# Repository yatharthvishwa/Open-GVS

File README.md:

# Open-GVS
control a person with gvs!!
this can control your balance by applying a controlled current to your mastoids, this project uses diy 3d printed electrodes which you can apply to your mastoids which are connected to the pcb
I was inspired to make this project because of a open sauce video https://www.youtube.com/watch?v=9Om2X6QcTgw

how to use?

📄 [View BOM](./GVS.csv)

electrode stl

PCB

Simulation

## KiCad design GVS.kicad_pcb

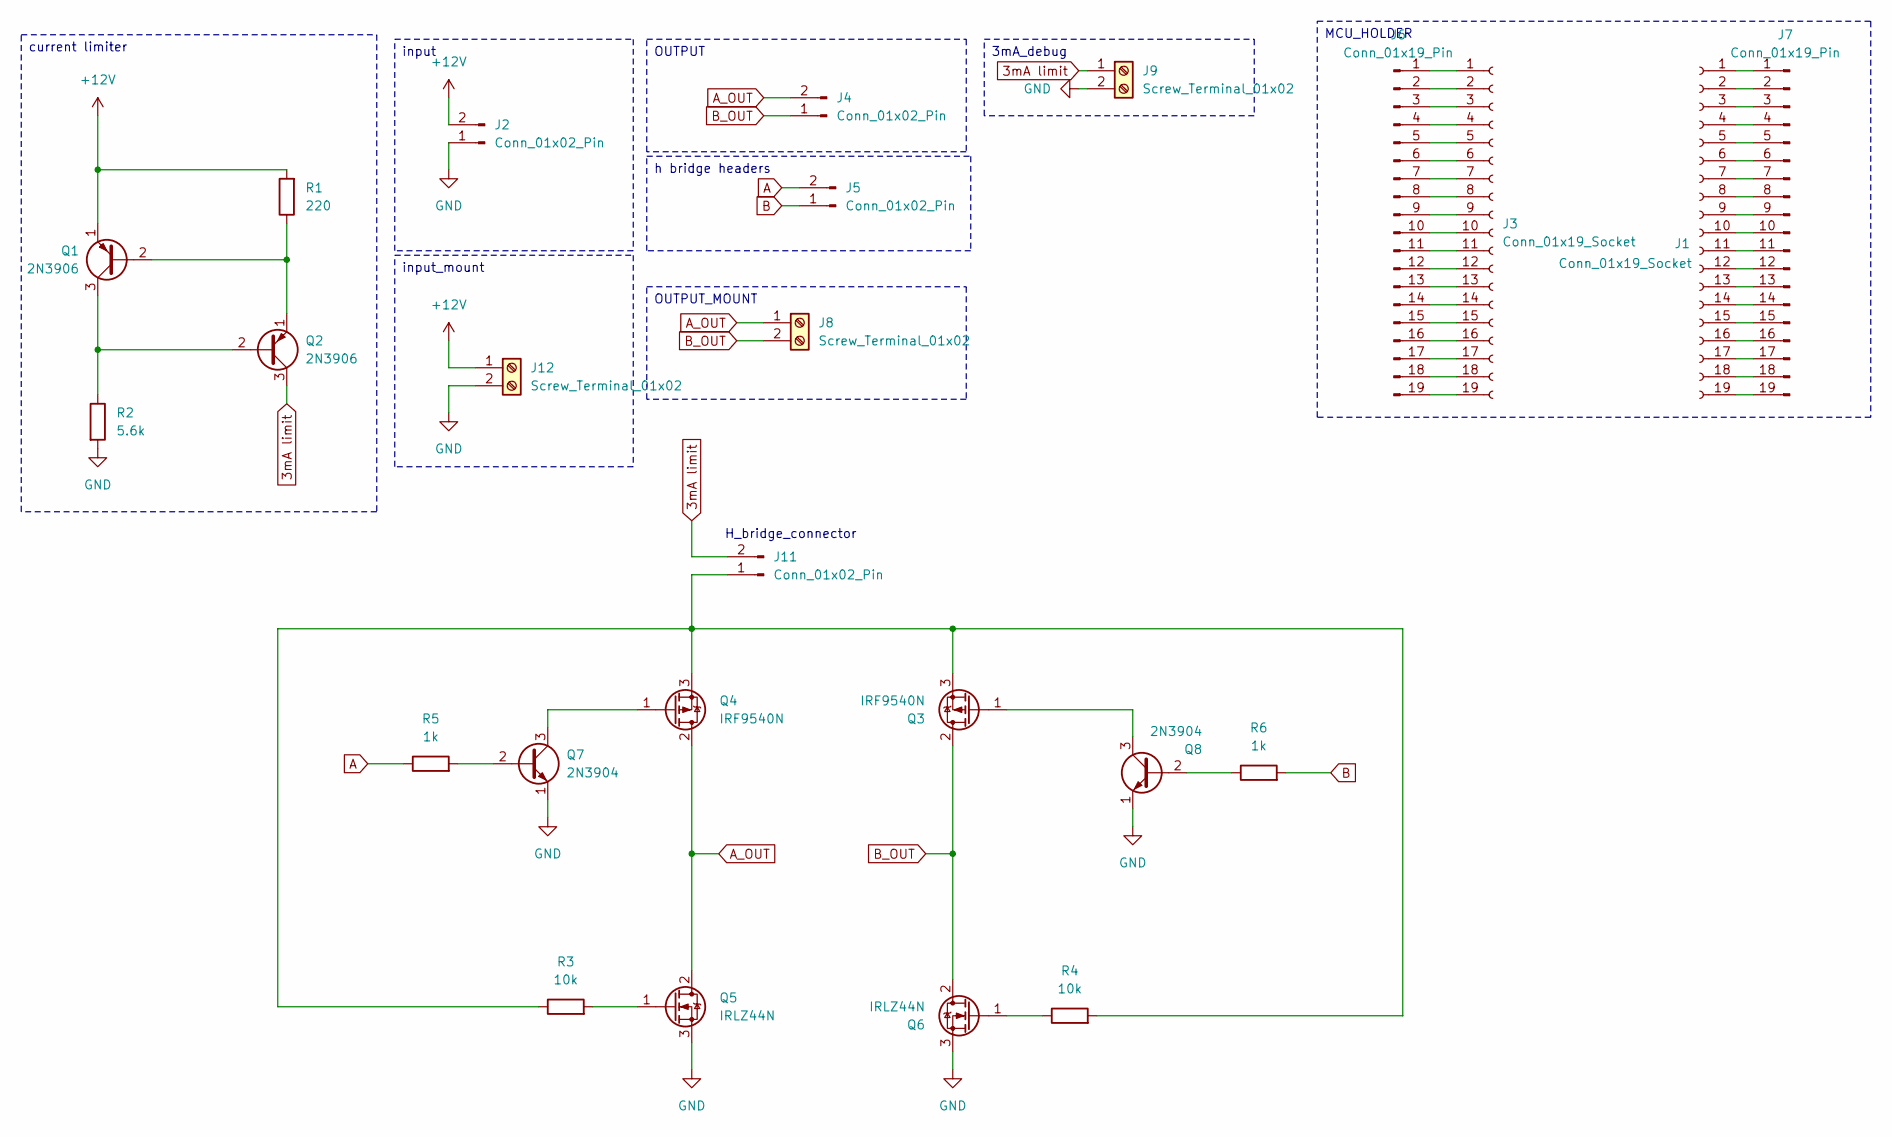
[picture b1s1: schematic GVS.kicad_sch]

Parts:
J1, J3: Conn_01x19_Socket; PinSocket_1x19_P2.54mm_Vertical
J2, J4, J5, J11: Conn_01x02_Pin; PinHeader_1x02_P2.54mm_Vertical
J6, J7: Conn_01x19_Pin; PinHeader_1x19_P2.54mm_Vertical
J8, J9, J12: Screw_Terminal_01x02; TerminalBlock_Xinya_XY308-2.54-2P_1x02_P2.54mm_Horizontal
Q1, Q2: 2N3906; TO-92_Inline
Q3, Q4: IRF9540N; TO-220-3_Vertical
Q5, Q6: IRLZ44N; TO-220-3_Vertical
Q7, Q8: 2N3904; TO-92_Inline
R1: 220; R_Axial_DIN0204_L3.6mm_D1.6mm_P2.54mm_Vertical
R2: 5.6k; R_Axial_DIN0204_L3.6mm_D1.6mm_P2.54mm_Vertical
R3, R4: 10k; R_Axial_DIN0204_L3.6mm_D1.6mm_P2.54mm_Vertical
R5, R6: 1k; R_Axial_DIN0204_L3.6mm_D1.6mm_P2.54mm_Vertical

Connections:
3mA limit: J9.1, J11.2, Q2.3 (C)
+12V: J2.2, J12.1, Q1.1 (E), R1.2
A: J5.2, R5.1
A_OUT: J4.2, J8.1, Q4.2 (D), Q5.2 (D)
B: J5.1, R6.2
B_OUT: J4.1, J8.2, Q3.2 (D), Q6.2 (D)
GND: J2.1, J9.2, J12.2, Q5.3 (S), Q6.3 (S), Q7.1 (E), Q8.1 (E), R2.2
unnamed: J1.1, J7.1
unnamed: J1.2, J7.2
unnamed: J1.3, J7.3
unnamed: J1.4, J7.4
unnamed: J1.5, J7.5
unnamed: J1.6, J7.6
unnamed: J1.7, J7.7
unnamed: J1.8, J7.8
unnamed: J1.9, J7.9
unnamed: J1.10, J7.10
unnamed: J1.11, J7.11
unnamed: J1.12, J7.12
unnamed: J1.13, J7.13
unnamed: J1.14, J7.14
unnamed: J1.15, J7.15
unnamed: J1.16, J7.16
unnamed: J1.17, J7.17
unnamed: J1.18, J7.18
unnamed: J1.19, J7.19
unnamed: J3.1, J6.1
unnamed: J3.2, J6.2
unnamed: J3.3, J6.3
unnamed: J3.4, J6.4
unnamed: J3.5, J6.5
unnamed: J3.6, J6.6
unnamed: J3.7, J6.7
unnamed: J3.8, J6.8
unnamed: J3.9, J6.9
unnamed: J3.10, J6.10
unnamed: J3.11, J6.11
unnamed: J3.12, J6.12
unnamed: J3.13, J6.13
unnamed: J3.14, J6.14
unnamed: J3.15, J6.15
unnamed: J3.16, J6.16
unnamed: J3.17, J6.17
unnamed: J3.18, J6.18
unnamed: J3.19, J6.19
unnamed: J11.1, Q3.3 (S), Q4.3 (S), R3.1, R4.2
unnamed: Q1.2 (B), Q2.1 (E), R1.1
unnamed: Q1.3 (C), Q2.2 (B), R2.1
unnamed: Q3.1 (G), Q8.3 (C)
unnamed: Q4.1 (G), Q7.3 (C)
unnamed: Q5.1 (G), R3.2
unnamed: Q6.1 (G), R4.1
unnamed: Q7.2 (B), R5.2
unnamed: Q8.2 (B), R6.1

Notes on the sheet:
H_bridge_connector
input_mount
3mA_debug
MCU_HOLDER
input
OUTPUT_MOUNT
h bridge headers
current limiter
OUTPUT

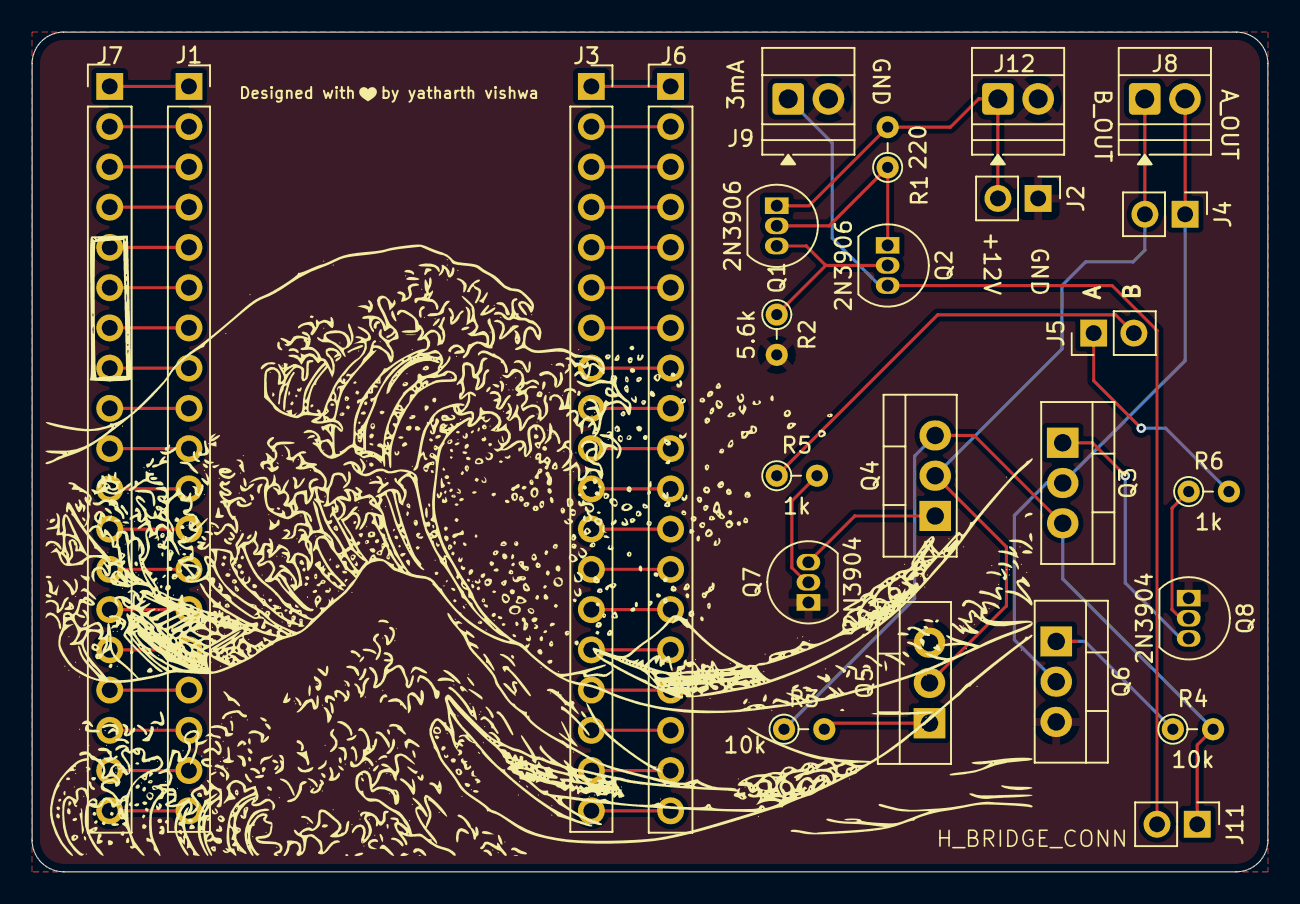
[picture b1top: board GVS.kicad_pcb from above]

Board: 2 copper layers, 78.0 x 53.0 mm, 25 parts (0 on the bottom side), 54 nets.

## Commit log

2026-01-25 inital commit
2026-01-25 added step files
2026-01-25 Update README to improve project description
2026-01-25 added firmware
2026-02-09 added screw terminals
2026-03-14 added BOM
2026-03-14 Add component details header to README
    Added a header for component details in the README.
2026-03-14 Update README to link to BOM and remove entries
    Removed detailed BOM entries and added a link to the BOM file.
2026-03-16 Add image to README
    Added an image to the README for visual reference.
2026-03-16 Rename Screenshot 2026-01-23 223440.png to Electrode
2026-03-16 Rename Screenshot 2026-01-23 225218.png to simulation
2026-03-16 Rename Screenshot 2026-02-09 174815.png to PCB
2026-03-16 Fix image link for Electrode in README
2026-03-16 Add images for electrode, PCB, and simulation
